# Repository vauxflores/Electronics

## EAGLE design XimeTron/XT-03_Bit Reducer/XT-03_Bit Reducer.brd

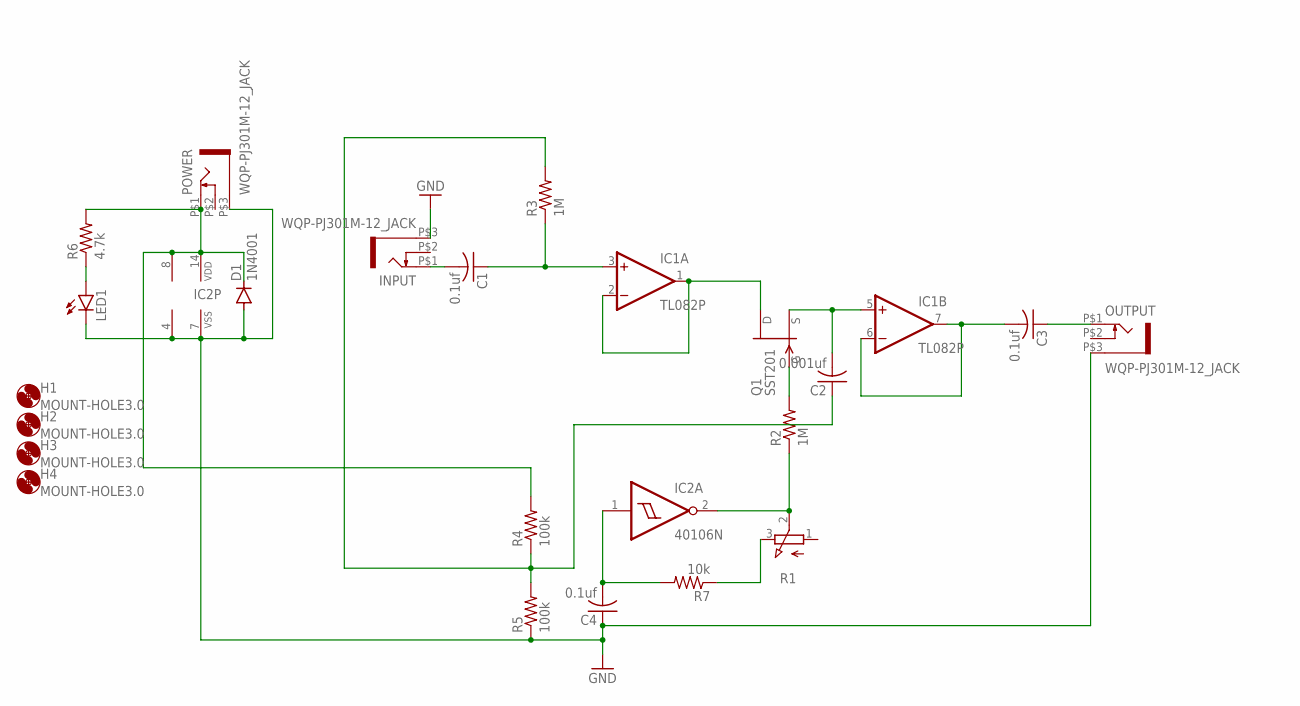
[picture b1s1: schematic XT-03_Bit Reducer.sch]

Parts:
C1, C3, C4: 0.1uf; C050-025X075
C2: 0.001uf; C050-025X075
D1: 1N4001; DO41-10
H1, H2, H3, H4: MOUNT-HOLE3.0; 3,0
IC1: TL082P; DIL08
IC2: 40106N; DIL14
INPUT: WQP-PJ301M-12_JACK
LED1: LED3MM
OUTPUT: WQP-PJ301M-12_JACK
POWER: WQP-PJ301M-12_JACK
Q1: SST201; SOT23
R1: EVUF2L; EVUFXL
R2, R3: 1M; 0207/7
R4, R5: 100k; 0207/7
R6: 4.7k; 0207/7
R7: 10k; 0207/7

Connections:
GND: C4.1, D1.A, IC1.4 (V-), IC2.7 (VSS), INPUT.P$3 (1), LED1.K (C), OUTPUT.P$3 (1), POWER.P$3 (1), R5.1
unnamed: Q1.3 (G), R2.2
unnamed: IC1.1 (OUT), IC1.2 (-IN), Q1.1 (D)
unnamed: C1.1, IC1.3 (+IN), R3.1
unnamed: C2.2, IC1.5 (+IN), Q1.2 (S)
unnamed: C3.2, IC1.6 (-IN), IC1.7 (OUT)
unnamed: C1.2, INPUT.P$1 (2)
unnamed: C2.1, R3.2, R4.1, R5.2
unnamed: C3.1, OUTPUT.P$1 (2)
unnamed: LED1.A, R6.1
unnamed: IC2.2 (O), R1.2 (S), R2.1
unnamed: R1.3 (E), R7.1
unnamed: C4.2, IC2.1 (I), R7.2
unnamed: D1.C, IC1.8 (V+), IC2.14 (VDD), POWER.P$1 (2), R4.2, R6.2

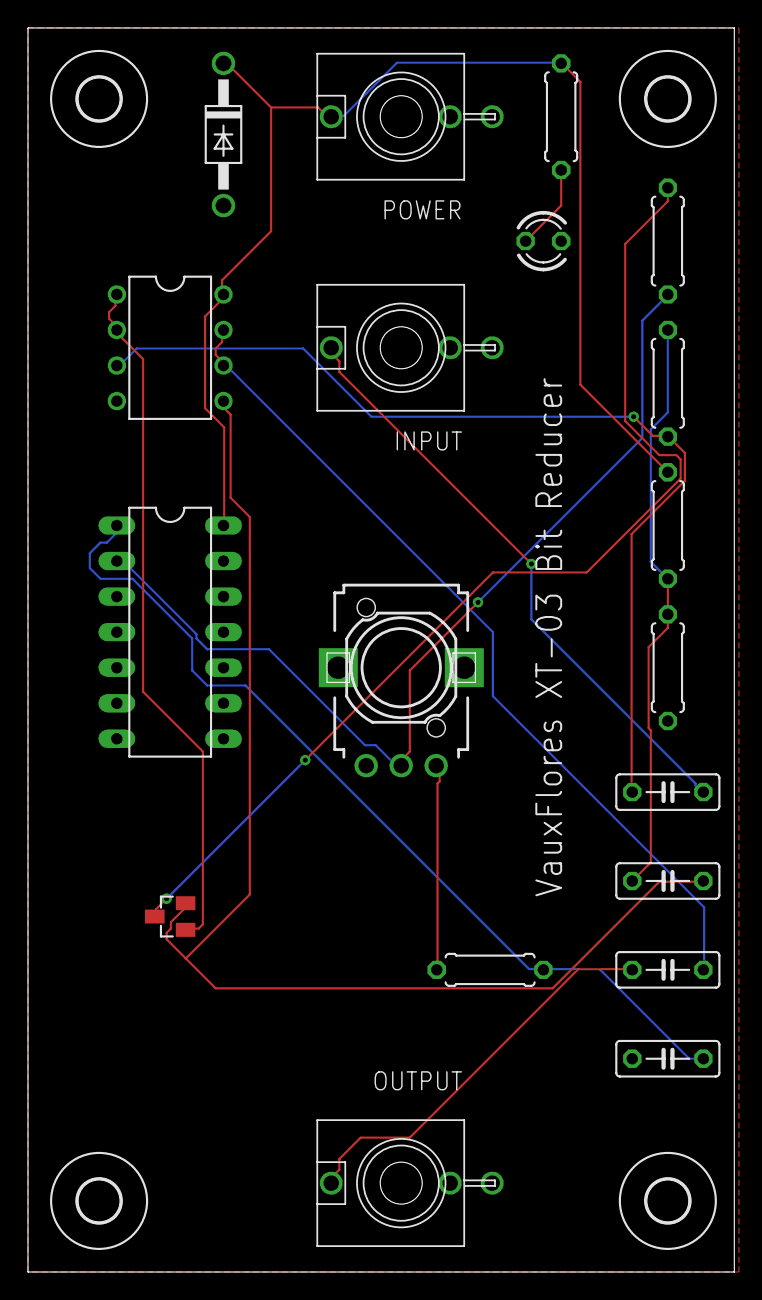
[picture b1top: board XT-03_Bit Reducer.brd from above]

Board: 2 copper layers, 50.5 x 88.9 mm, 23 parts (0 on the bottom side), 14 nets.

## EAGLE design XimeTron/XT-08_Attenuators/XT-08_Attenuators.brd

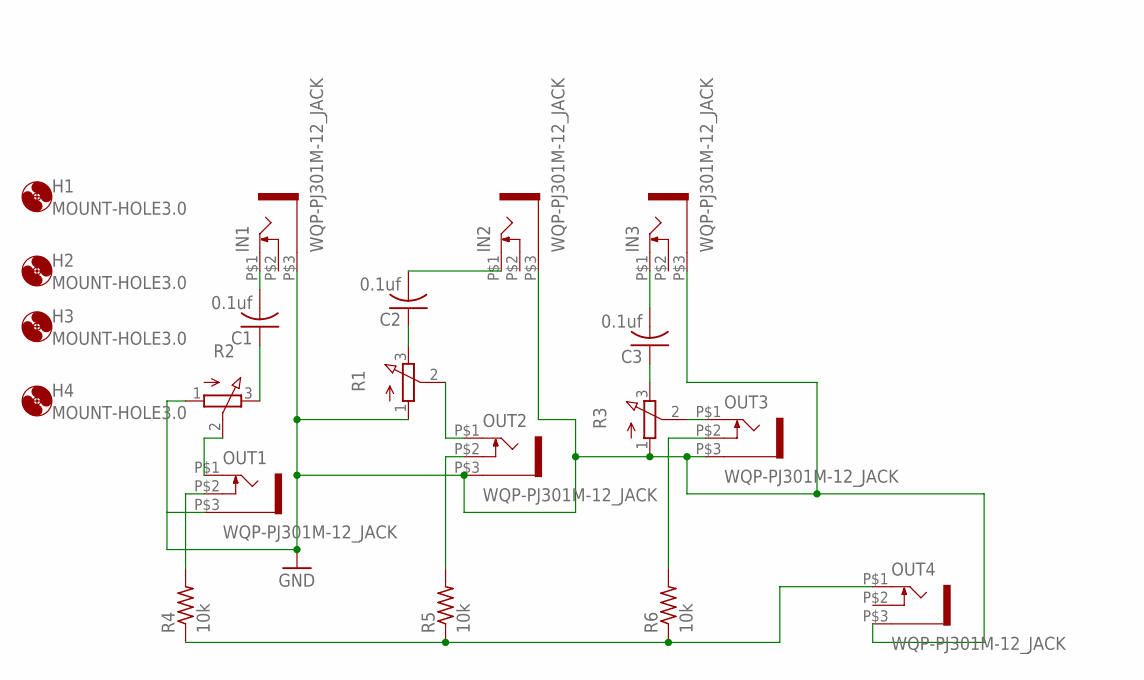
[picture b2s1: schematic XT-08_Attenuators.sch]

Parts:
C1, C2, C3: 0.1uf; C050-025X075
H1, H2, H3, H4: MOUNT-HOLE3.0; 3,0
IN1, IN2, IN3: WQP-PJ301M-12_JACK
OUT1, OUT2, OUT3, OUT4: WQP-PJ301M-12_JACK
R1, R2, R3: EVUF2L; EVUFXL
R4, R5, R6: 10k; 0204/7

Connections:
GND: IN1.P$3 (1), IN2.P$3 (1), IN3.P$3 (1), OUT1.P$3 (1), OUT2.P$3 (1), OUT3.P$3 (1), OUT4.P$3 (1), R1.1 (A), R2.1 (A), R3.1 (A)
unnamed: C1.2, IN1.P$1 (2)
unnamed: C2.1, R1.3 (E)
unnamed: OUT2.P$1 (2), R1.2 (S)
unnamed: C2.2, IN2.P$1 (2)
unnamed: C1.1, R2.3 (E)
unnamed: OUT1.P$1 (2), R2.2 (S)
unnamed: C3.2, IN3.P$1 (2)
unnamed: C3.1, R3.3 (E)
unnamed: OUT3.P$1 (2), R3.2 (S)
unnamed: OUT1.P$2 (3), R4.2
unnamed: OUT2.P$2 (3), R5.2
unnamed: OUT3.P$2 (3), R6.2
unnamed: OUT4.P$1 (2), R4.1, R5.1, R6.1

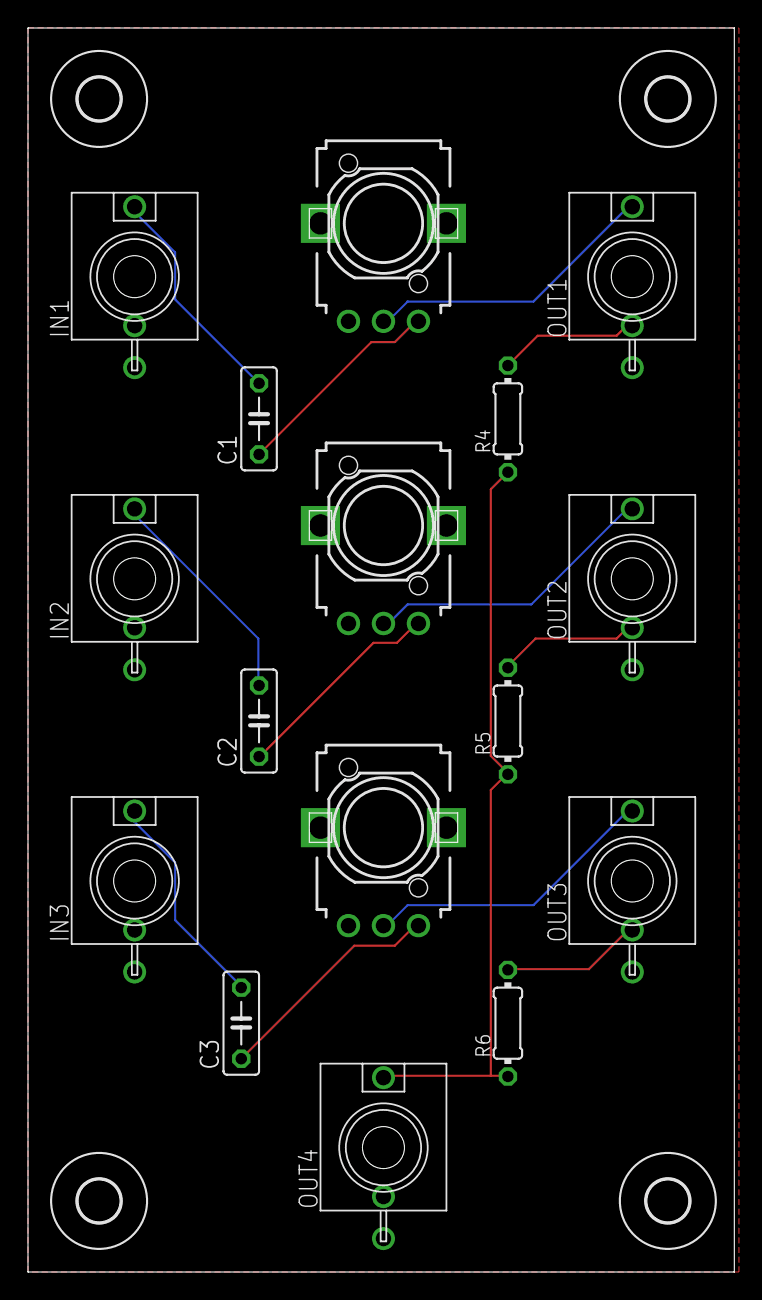
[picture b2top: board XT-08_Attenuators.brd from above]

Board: 2 copper layers, 50.5 x 88.9 mm, 20 parts (0 on the bottom side), 14 nets.

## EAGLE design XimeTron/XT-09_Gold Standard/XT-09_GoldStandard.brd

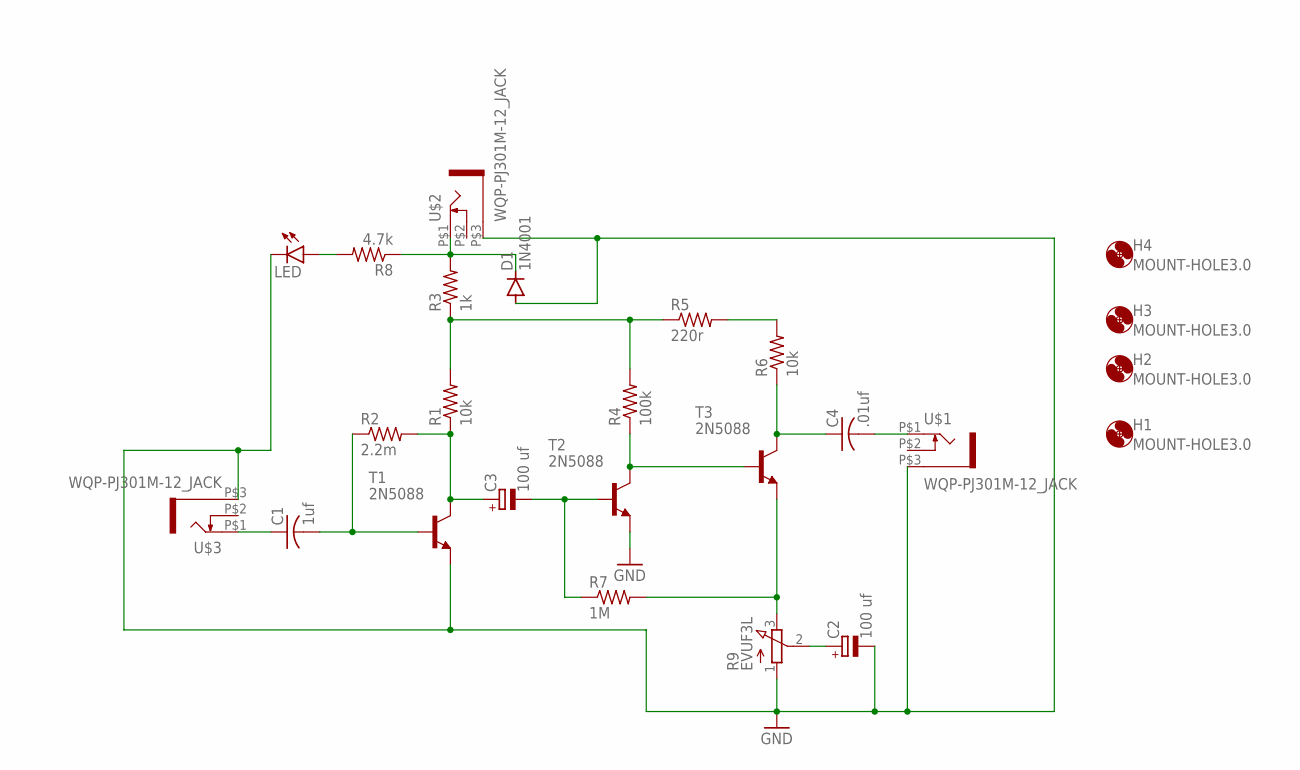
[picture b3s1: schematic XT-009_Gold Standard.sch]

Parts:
C1: 1uf; C050-025X075
C2, C3: 100 uf; E2,5-7
C4: .01uf; C050-025X075
D1: 1N4001; DO41-10
H1, H2, H3, H4: MOUNT-HOLE3.0; 3,0
LED: LED3MM
R1, R6: 10k; 0207/7
R2: 2.2m; 0207/7
R3: 1k; 0207/7
R4: 100k; 0207/7
R5: 220r; 0207/7
R7: 1M; 0207/7
R8: 4.7k; 0207/7
R9: EVUF3L; EVUFXL
T1, T2, T3: 2N5088; TO92
U$1, U$2, U$3: WQP-PJ301M-12_JACK

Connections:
GND: C2.-, D1.A, LED.K (C), R9.1 (A), T1.3 (E), T2.3 (E), U$1.P$3 (1), U$2.P$3 (1), U$3.P$3 (1)
unnamed: C1.2, R2.1, T1.2 (B)
unnamed: C3.+, R1.1, R2.2, T1.1 (C)
unnamed: R1.2, R3.1, R4.2, R5.1
unnamed: C1.1, U$3.P$1 (2)
unnamed: LED.A, R8.2
unnamed: C3.-, R7.1, T2.2 (B)
unnamed: R4.1, T2.1 (C), T3.2 (B)
unnamed: R5.2, R6.2
unnamed: C4.1, R6.1, T3.1 (C)
unnamed: C4.2, U$1.P$1 (2)
unnamed: C2.+, R9.2 (S)
unnamed: D1.C, R3.2, R8.1, U$2.P$1 (2)
unnamed: R7.2, R9.3 (E), T3.3 (E)

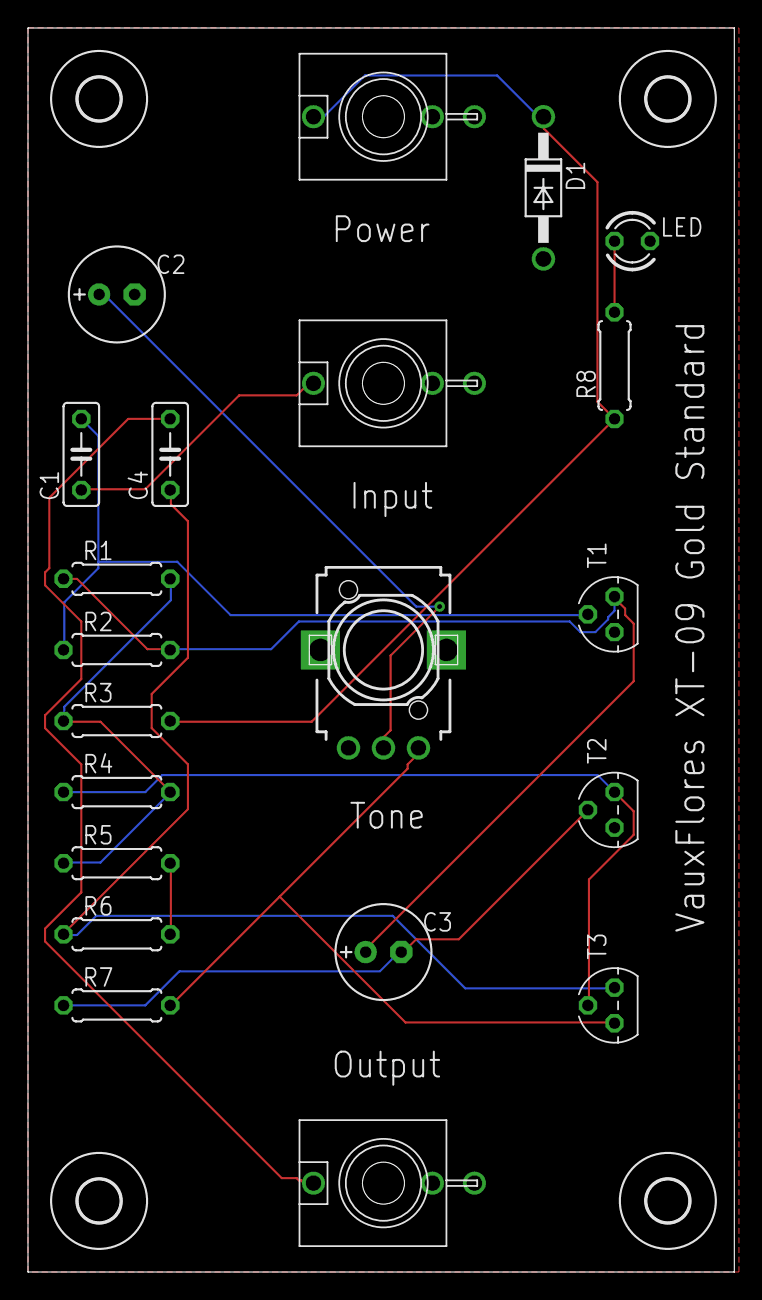
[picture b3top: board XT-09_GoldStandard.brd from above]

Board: 2 copper layers, 50.5 x 88.9 mm, 25 parts (0 on the bottom side), 14 nets.
